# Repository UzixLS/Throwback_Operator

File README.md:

# THROWBACK OPERATOR
OPL3 VGM player powered by STM32

This project is a hardware video game music (VGM) player that uses a genuine YMF262 (OPL3) sound chip and its accompanying YAC512 DAC.
There is no emulation here. This is the real chip.

Included in this repository is the complete schematic, firmware source, and KiCAD board files. Feel free to make your own board, but please don't resell them :)

If you would like to purchase an official complete Throwback Operator board, you can order one from me here: https://www.aidanlawrence.com/product/throwback-operator/

# Information About the Main Sound Chips and VGM

The YMF262, also known as the Operator Type L3 (OPL3), is an 18-channel FM sound chip that was commonly found inside of personal computers in the mid to late 1990's.
Most notably, the OPL3 was found on the Sound Blaster Pro 2 and the Sound Blaster 16.
The OPL3 is backwards compatible with the OPL2 (YM3812). The OPL2 is backwards compatible with the original OPL (YM3526).
This means that the Throwback Operator is capable of playing back OPL3, OPL2, and OPL tracks. The OPL2 was found on the original Adlib and Sound Blaster cards.
The OPL was usually found within arcade machines.

The clock signal for the YMF262 is dynamically generated from the microcontroller. The timers on this particular board only have 16-bit resolution, so VGMs with exotic frequencies may not sound perfectly in tune. Standard clock OPL2 and OPL3 VGMs will often sound just fine though.

VGM stands for Video Game Music, and it is a 44.1KHz logging format that stores real sound chip register information. My player will parse these files and send the data to the appropriate chips. You can learn more about the VGM file format here: http://www.smspower.org/Music/VGMFileFormat

http://www.smspower.org/uploads/Music/vgmspec170.txt?sid=58da937e68300c059412b536d4db2ca0

# Schematic

# SD Card Information

The Throwback Operator accepts MicroSD cards formatted as FAT32. Your SD card must only contain uncompressed .vgm files. VGZ FILES WILL NOT WORK! You may download .vgz files and use 7zip to extract the uncompressed file out of them. Vgm files on the SD card do not need to have the .vgm extension. As long as they contain valid, uncompressed vgm data, they will be read by the program regardless of their name. You can find VGM files by Googling "myGameName VGM," or by checking out sites like http://vgmrips.net/packs/

# Control Over Serial
You can use a serial connection to control playback features. The commands are as follows:

Command | Result
------------ | -------------
\+ | Next Track
\- | Previous Track
\* | Random Track
\/ | Toggle Shuffle Mode
\. | Toggle Song Looping
r: | Request song
? | What song is playing?
\! | Toggle the OLED display

A song request is formatted as follows: ```r:mySongFile.vgm```
Once a song request is sent through the serial console, an attempt will be made to open that song file. The file must exist on the SD card, and spelling/capitalization must be correct.
Need an easy-to-use serial console? [I've made one here.](https://github.com/AidanHockey5/OpenArduinoSerialConsole)

# Programming the Microcontroller

The on-board microcontroller is a STM32F103C8T6, the same microcontroller found on the popular "blue pill" development boards. 
Therefore, programming the Throwback Operator boards is fairly similar.
The firmware was built with Visual Studio Code with the PlatformIO extension installed.

Programming over Serial:
* Connect your Throwback Operator board to your computers USB port.
* Ensure that you have the CH340 driver installed. Windows 10 should have this automatically, otherwise, [grab the driver here](https://sparks.gogo.co.nz/ch340.html)
* Ensure nothing else is currently connected to your board over serial.
* On the top of the board, you will see two black jumpers. By default, these jumpers are both in the "Down" position (middle pin and bottom pin jumped).
* Remove the left jumper and reattach it to the "Up" position (middle pin and top pin jumped).
* Press the RESET button on the Throwback Operator board

* You can either program the device with the flashing tool linked below, or from the source code.

[DOWNLOAD THE FLASHING TOOL HERE](https://www.aidanlawrence.com/tools/ee/tbo/Megaflasher_Throwback_Operator.zip)

* Windows users are reccomended to run the pre-compiled "Flash.exe" file.
  All other operating system users must run the Flash.py file. 
  Dependancies and instructions are listed in the Readme file.
* After successfully running the flashing tool, you are done and don't need to continue with the following instructions.

If you plan to build from the source code instead:
* In VS Code (or whatever your IDE of choice is), navigate to the `platformio.ini` and ensure the upload protocol is set to `serial`
* Hit the upload button (Arrow icon in the bottom bar of VS code)
* Once your code is uploaded, replace the left jumper to its original "Down" position 

# Troubleshooting

Occasionally, when the player is first plugged in, it will hang or get caught in a boot-loop. Plugging in a USB cable gives breif moments of unstable power when the contacts inside of the connector are jostling against eachother which may place the SD card in an unknown state. Simply disconnect and reconnect the USB cable if you are caught in a bootloop.

This player is for OPL-family VGMs only. That means you can play any VGM file that contains data for the YM3526 (OPL), YM3812 (OPL2) or the YMF262 (OPL3).

Ensure that your VGM files are uncompressed. VGZ files will not work. Simply use 7zip on VGM files to extract the VGM files within.

Make sure your SD card is formatted to FAT32 and only contains VGM files. Folders are not supported.

# Looking for an Enclosure for your Player?

Voodle has contributed a 3D-printable enclosure for the Throwback Operator!
https://www.thingiverse.com/thing:4577831

Thanks, Voodle!

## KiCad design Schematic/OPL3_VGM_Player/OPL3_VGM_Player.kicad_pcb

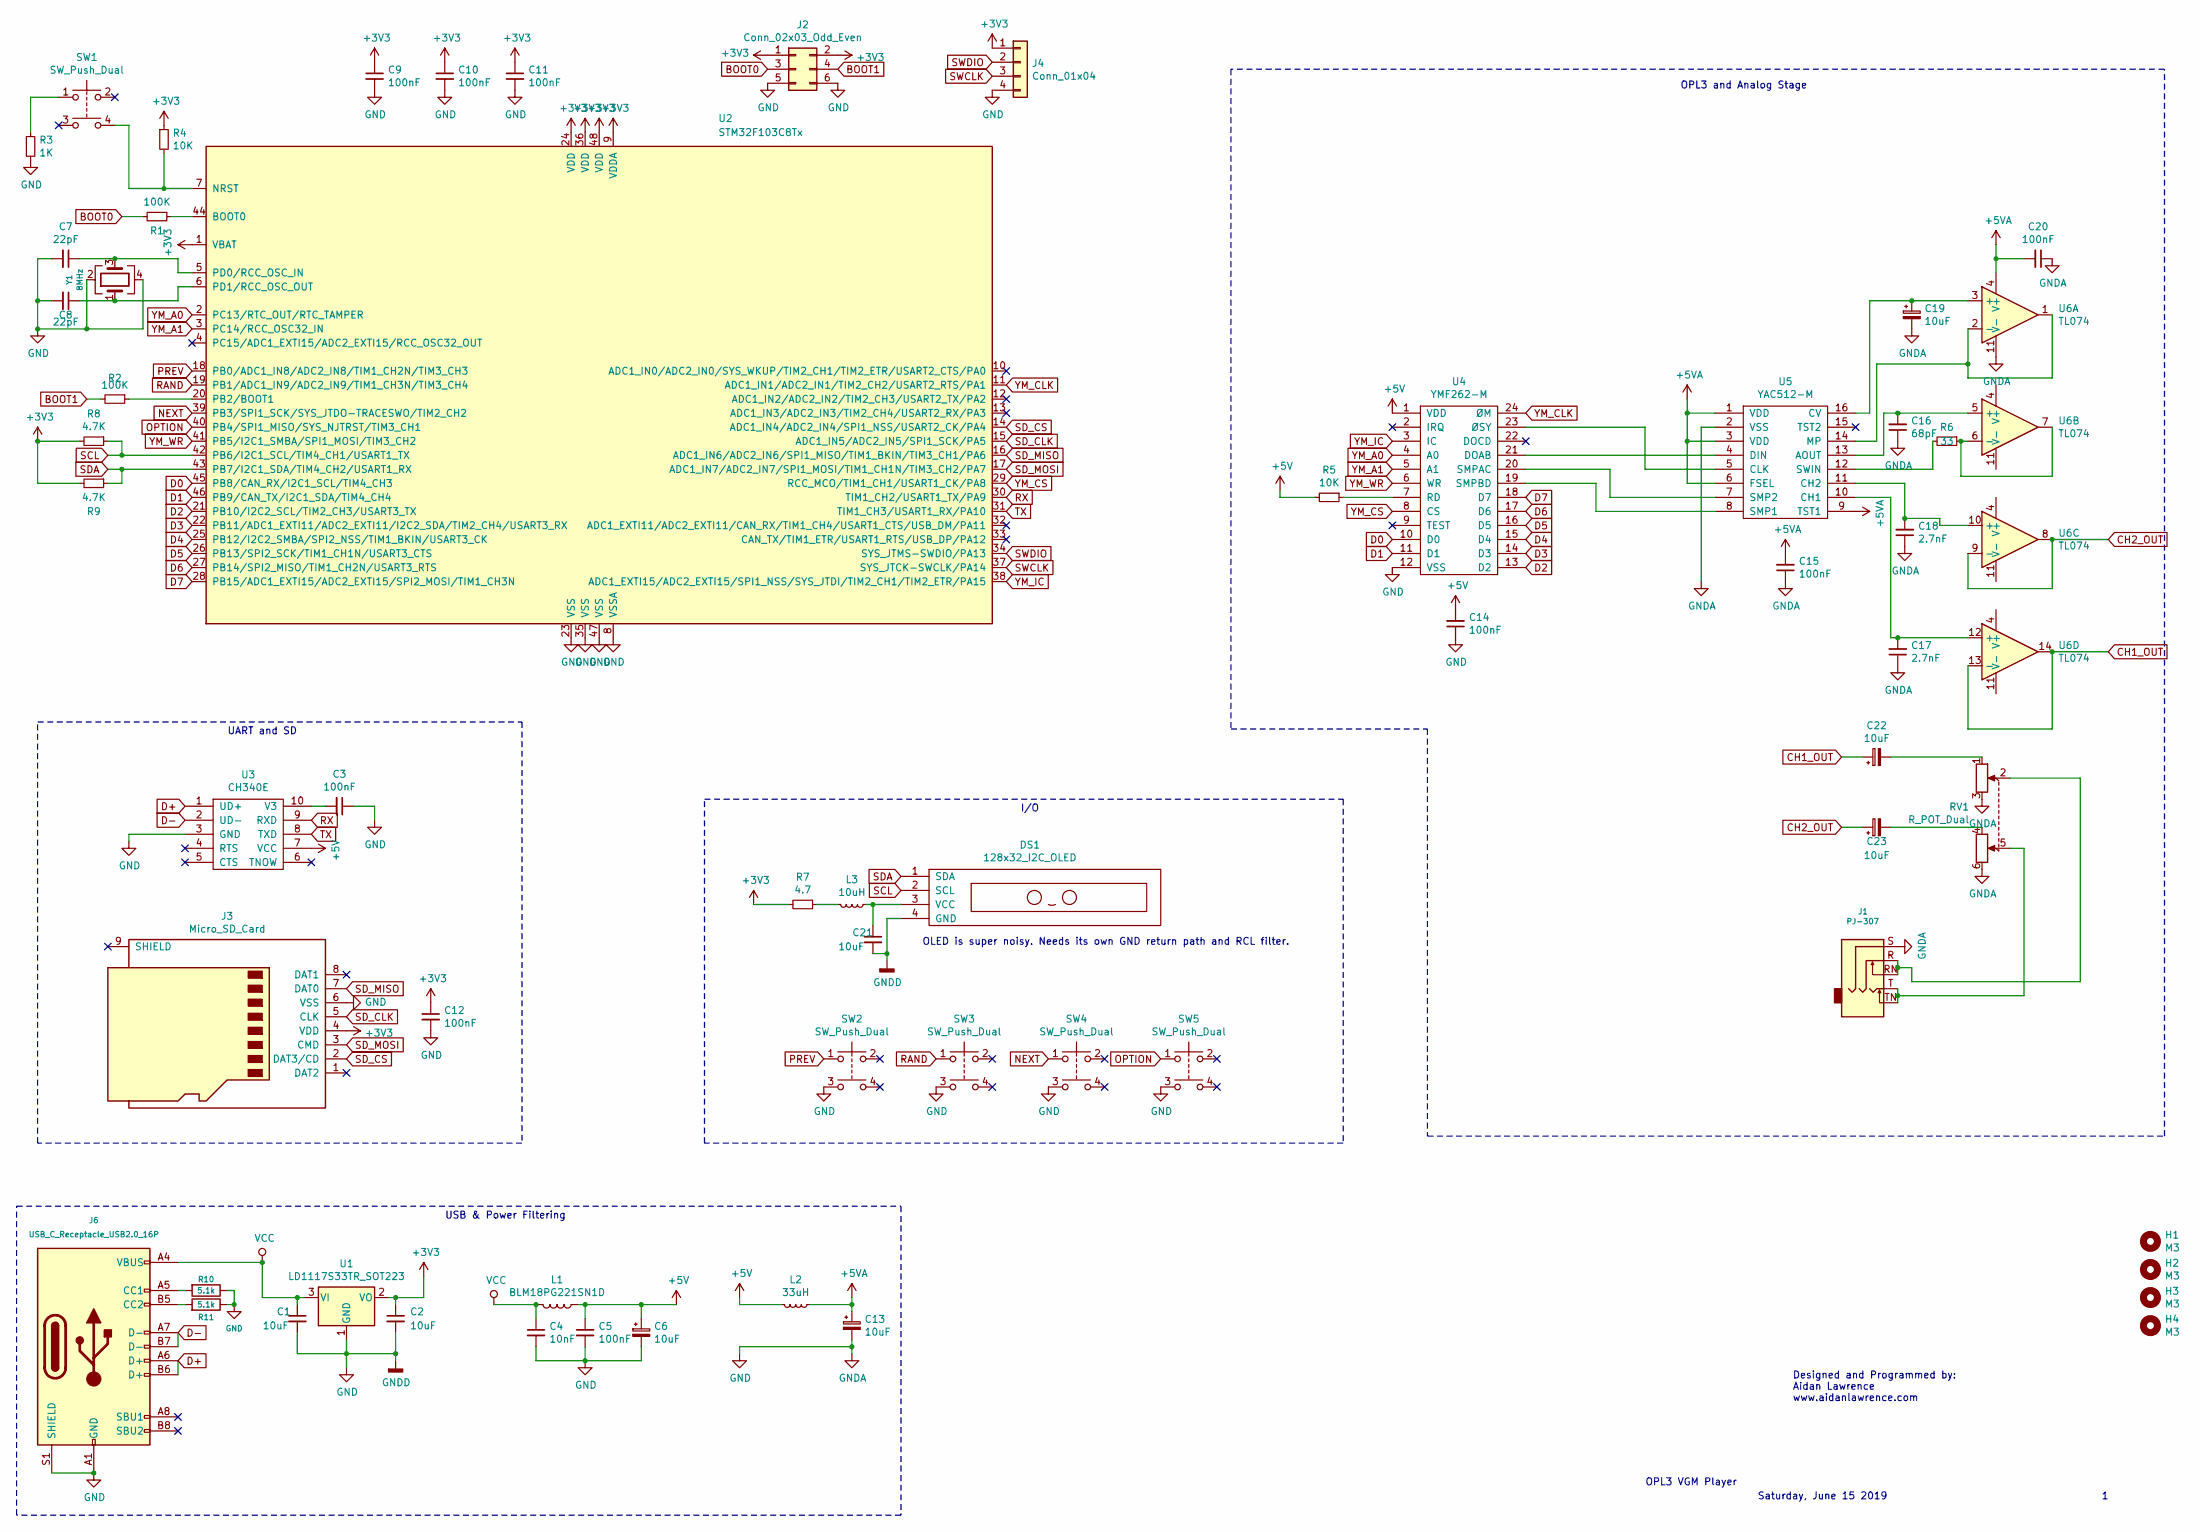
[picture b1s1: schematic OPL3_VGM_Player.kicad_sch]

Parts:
C1, C2, C21: 10uF; C_1206
C3, C5, C9, C10, C11, C12, C14, C15, C20: 100nF; C_0805
C4: 10nF; C_0805
C6, C13, C19, C22, C23: 10uF; C_1206_3216Metric
C7, C8: 22pF; C_0603
C16: 68pF; C_0603
C17, C18: 2.7nF; C_0603
DS1: 128x32_I2C_OLED; 128x32_OLED_I2C_Module
H1, H2, H3, H4: M3; MountingHole_3.2mm_M3
J1: PJ-307
J2: Conn_02x03_Odd_Even; Pin_Header_Straight_2x03_Pitch2.54mm
J3: Micro_SD_Card; GCT-MEM2055-00-190-01-A
J4: Conn_01x04; Pin_Header_Straight_1x04_Pitch2.54mm
J6: USB_C_Receptacle_USB2.0_16P; USB_C_Receptacle_HRO_TYPE-C-31-M-12
L1: BLM18PG221SN1D; L_0603_1608Metric_Pad1.05x0.95mm_HandSolder
L2: 33uH; L_4x4
L3: 10uH; L_4x4
R1, R2: 100K; R_0805
R3: 1K; R_0805
R4, R5: 10K; R_0805
R6: 33; R_0805
R7: 4.7; R_0805
R8, R9: 4.7K; R_0805
R10, R11: 5.1k; R_0603_1608Metric_Pad0.98x0.95mm_HandSolder
RV1: R_POT_Dual; Potentiometer_Alps_RK097_Double_Vertical
SW1, SW2, SW3, SW4, SW5: SW_Push_Dual; SW_TH_Tactile_Omron_B3F-10xx
U1: LD1117S33TR_SOT223; SOT-223-3_TabPin2
U2: STM32F103C8Tx; LQFP-48_7x7mm_Pitch0.5mm
U3: CH340E; MSOP-10_3x3mm_Pitch0.5mm
U4: YMF262-M; SOIC-24W_7.5x15.4mm_Pitch1.27mm
U5: YAC512-M; SOIC-16W_5.3x10.2mm_Pitch1.27mm
U6: TL074; SOIC-14_3.9x8.7mm_Pitch1.27mm
Y1: 8MHz; Crystal_SMD_SeikoEpson_TSX3225-4Pin_3.2x2.5mm_HandSoldering

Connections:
+3V3: C2.1, C9.1, C10.1, C11.1, C12.1, J2.1, J2.2, J3.4 (VDD), J4.1, R4.1, R7.2, R8.2, R9.2, U1.2 (VO), U2.1 (VBAT), U2.9 (VDDA), U2.24 (VDD), U2.36 (VDD), U2.48 (VDD)
+5V: C5.1, C6.1, C14.2, L1.1, L2.2, R5.2, U3.7 (VCC), U4.1 (VDD)
+5VA: C13.1, C15.2, C20.2, L2.1, U5.1 (VDD), U5.3 (VDD), U5.6 (FSEL), U5.9 (TST1), U6.4 (V+)
BOOT0: J2.3, R1.2
BOOT1: J2.4, R2.2
CH1_OUT: C22.1, U6.13 (-), U6.14
CH2_OUT: C23.1, U6.8, U6.9 (-)
D0: U2.45 (PB8/CAN_RX/I2C1_SCL/TIM4_CH3), U4.10 (D0)
D1: U2.46 (PB9/CAN_TX/I2C1_SDA/TIM4_CH4), U4.11 (D1)
D2: U2.21 (PB10/I2C2_SCL/TIM2_CH3/USART3_TX), U4.13 (D2)
D3: U2.22 (PB11/ADC1_EXTI11/ADC2_EXTI11/I2C2_SDA/T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), U4.14 (D3)
D4: U2.25 (PB12/I2C2_SMBA/SPI2_NSS/TIM1_BKIN/USART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), U4.15 (D4)
D5: U2.26 (PB13/SPI2_SCK/TIM1_CH1N/USART3_CTS), U4.16 (D5)
D6: U2.27 (PB14/SPI2_MISO/TIM1_CH2N/USART3_RTS), U4.17 (D6)
D7: U2.28 (PB15/ADC1_EXTI15/ADC2_EXTI15/SPI2_MOSI/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), U4.18 (D7)
D+: J6.A6 (D+), J6.B6 (D+), U3.1 (UD+)
D-: J6.A7 (D-), J6.B7 (D-), U3.2 (UD-)
GND: C1.2, C2.2, C3.1, C4.2, C5.2, C6.2, C7.2, C8.2, C9.2, C10.2, C11.2, C12.2, C13.2, C14.1, C15.1, C16.1, C17.1, C18.1, C19.2, C20.1, C21.2, DS1.4 (GND), J1.S, J2.5, J2.6, J3.6 (VSS), J4.4, J6.A1 (GND), J6.A12 (GND), J6.B1 (GND), J6.B12 (GND), J6.S1 (SHIELD), R3.2, R10.1, R11.1, RV1.3, RV1.6, SW2.3, SW3.3, SW4.3, SW5.3, U1.1 (GND), U2.8 (VSSA), U2.23 (VSS), U2.35 (VSS), U2.47 (VSS), U3.3 (GND), U4.12 (VSS), U5.2 (VSS), U6.11 (V-), Y1.2, Y1.4
NEXT: SW4.1, U2.39 (PB3/SPI1_SCK/SYS_JTDO-TRACESWO/TIM2_CH2)
unnamed: C22.2, RV1.1
unnamed: C23.2, RV1.4
unnamed: C21.1, DS1.3 (VCC), L3.1
unnamed: J1.R, J1.RN, RV1.2
unnamed: J1.T, J1.TN, RV1.5
unnamed: J6.A5 (CC1), R10.2
unnamed: J6.B5 (CC2), R11.2
unnamed: L3.2, R7.1
unnamed: R3.1, SW1.1
unnamed: R1.1, U2.44 (BOOT0)
unnamed: R4.2, SW1.4, U2.7 (NRST)
unnamed: R2.1, U2.20 (PB2/BOOT1)
unnamed: C7.1, U2.5 (PD0/RCC_OSC_IN), Y1.3
unnamed: C8.1, U2.6 (PD1/RCC_OSC_OUT), Y1.1
unnamed: C3.2, U3.10 (V3)
unnamed: U4.21 (DOAB), U5.4 (DIN)
unnamed: R5.1, U4.7 (RD)
unnamed: U4.20 (SMPAC), U5.7 (SMP2)
unnamed: U4.19 (SMPBD), U5.8 (SMP1)
unnamed: U4.23 (ØSY), U5.5 (CLK)
unnamed: C16.2, U5.13 (AOUT), U6.5 (+)
unnamed: C17.2, U5.10 (CH1), U6.12 (+)
unnamed: C18.2, U5.11 (CH2), U6.10 (+)
unnamed: C19.1, U5.16 (CV), U6.3 (+)
unnamed: U5.14 (MP), U6.1, U6.2 (-)
unnamed: R6.2, U5.12 (SWIN)
unnamed: R6.1, U6.6 (-), U6.7
OPTION: SW5.1, U2.40 (PB4/SPI1_MISO/SYS_NJTRST/TIM3_CH1)
PREV: SW2.1, U2.18 (PB0/ADC1_IN8/ADC2_IN8/TIM1_CH2N/TIM3_CH3)
RAND: SW3.1, U2.19 (PB1/ADC1_IN9/ADC2_IN9/TIM1_CH3N/TIM3_CH4)
RX: U2.30 (TIM1_CH2/USART1_TX/PA9), U3.9 (RXD)
SCL: DS1.2 (SCL), R8.1, U2.42 (PB6/I2C1_SCL/TIM4_CH1/USART1_TX)
SDA: DS1.1 (SDA), R9.1, U2.43 (PB7/I2C1_SDA/TIM4_CH2/USART1_RX)
SD_CLK: J3.5 (CLK), U2.15 (ADC1_IN5/ADC2_IN5/SPI1_SCK/PA5)
SD_CS: J3.2 (DAT3/CD), U2.14 (ADC1_IN4/ADC2_IN4/SPI1_NSS/USART2_CK/PA4)
SD_MISO: J3.7 (DAT0), U2.16 (ADC1_IN6/ADC2_IN6/SPI1_MISO/TIM1_BKIN/T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)
SD_MOSI: J3.3 (CMD), U2.17 (ADC1_IN7/ADC2_IN7/SPI1_MOSI/TIM1_CH1N/T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)
SWCLK: J4.3, U2.37 (SYS_JTCK-SWCLK/PA14)
SWDIO: J4.2, U2.34 (SYS_JTMS-SWDIO/PA13)
TX: U2.31 (TIM1_CH3/USART1_RX/PA10), U3.8 (TXD)
VCC: C1.1, C4.1, J6.A4 (VBUS), J6.A9 (VBUS), J6.B4 (VBUS), J6.B9 (VBUS), L1.2, U1.3 (VI)
YM_A0: U2.2 (PC13/RTC_OUT/RTC_TAMPER), U4.4 (A0)
YM_A1: U2.3 (PC14/RCC_OSC32_IN), U4.5 (A1)
YM_CLK: U2.11 (ADC1_IN1/ADC2_IN1/TIM2_CH2/USART2_RTS/P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), U4.24 (ØM)
YM_CS: U2.29 (RCC_MCO/TIM1_CH1/USART1_CK/PA8), U4.8 (CS)
YM_IC: U2.38 (ADC1_EXTI15/ADC2_EXTI15/SPI1_NSS/SYS_JT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), U4.3 (IC)
YM_WR: U2.41 (PB5/I2C1_SMBA/SPI1_MOSI/TIM3_CH2), U4.6 (WR)

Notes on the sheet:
OPL3 and Analog Stage
Saturday, June 15 2019
OPL3 VGM Player
Designed and Programmed by: Aidan Lawrence www.aidanlawrence.com
I/O
USB & Power Filtering
UART and SD
OLED is super noisy. Needs its own GND return path and RCL filter.

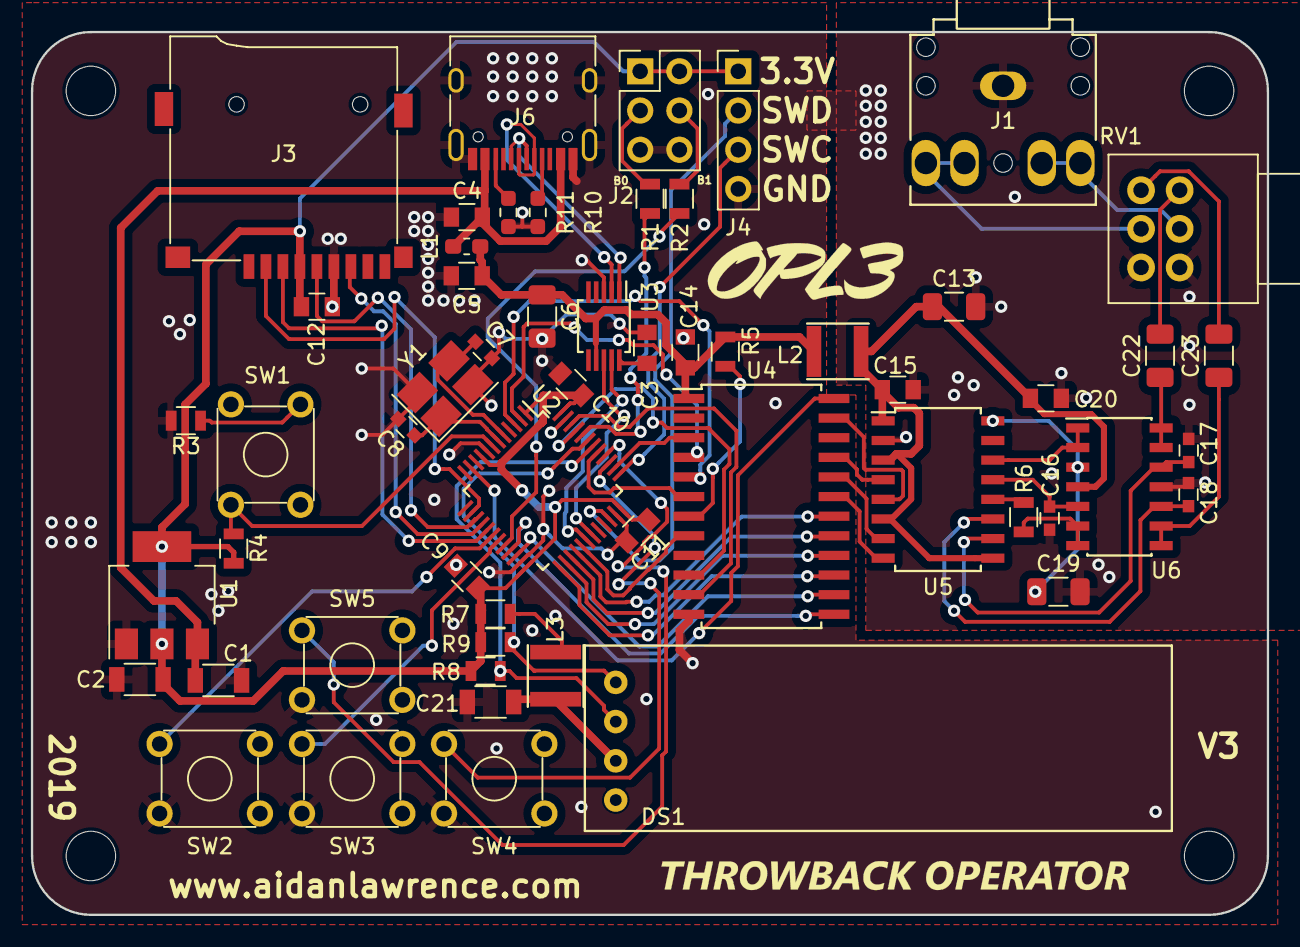
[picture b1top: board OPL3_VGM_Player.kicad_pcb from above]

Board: 2 copper layers, 80.0 x 57.2 mm, 60 parts (0 on the bottom side), 66 nets.

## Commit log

2024-03-27 pcb 2024.0
